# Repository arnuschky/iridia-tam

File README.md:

IRIDIA-TAM
==========

The IRIDIA TAM (Task Abstraction Module), a device whose function is to represent tasks that have to be performed by e-puck robots in laboratory experiments.

 * Website: http://arnuschky.github.com/iridia-tam/  
 * GitHub: https://github.com/arnuschky/iridia-tam/  
 * Repository: http://arnuschky.github.com/iridia-tam/  
 
Current version of the TAM: version 5, revision D.

The GitHub repository contains all files required for producing and using the TAM. In detail, the different directories contain:

3dmodel
-------

A 3D model of the TAM, created by using the free version of Google Sketchup (version 8). Models of the PCBs have been created using EagleUp (http://eagleup.wordpress.com/).

Additionally, the directory contains 2D plans of the plastic shell in PDF format. These plans were used to produce the plastic shell (machined from POM plastic).

coordinator
----------

This directory contains the coordinator, the central software written in Java that controls all TAMs in a given experiment. The researcher can use the coordinator software to set the behavior of the TAMs, define their interrelationships and collect statistics. Due to the use of Java, the software it platform-independent.

The directory also includes a modified version of the Xbee-api, an open-source project to access Xbee modules using Java. See http://code.google.com/p/xbee-api/ for more information. The project has been adapted to use the Digimesh mesh networking prototcol. If desired, one could also use simple point-to-point communication or the more advanced Zigbee prototcol.

electronics
-----------

This directory contains the project files created using Eagle (non-free version, due to PCB size) and the Arduino libraries and firmware.

### electronics/eagle

Contains the CAD files (board and schematics) for CADSoft Eagle (Version 6). 
Additionally, a library with custom footprints is also included in the repository.

### electronics/arduino

Sourcecode of the TAM's firmware ("sketchbook" in Arduino-speech). There are also a number of libraries included on which the firmware depends. Some of these libraries have been written or modified by us:

 - ircom - library that allows to communicate between the TAM and the epuck using the proximity sensor of the epuck
 - TLC59116 - generic TLC59116 library, adapted from http://brmlab.cz/project/ledbar (CC Attribution-Noncommercial-Share Alike 3.0 Unported License)
 - Xbee - library for using Xbee modules with the Arduino by Andrew Rapp, adapted to work with Digimesh networks and software serial ports (GPL 3)

Others are 3rd party open-source projects included for convenience:

 - I2C - fast I2C library by Wayne Truchsess (LGPL) http://dsscircuits.com/articles/arduino-i2c-master-library.html

photos
------

High-res photos of the TAM version 5, revision D.

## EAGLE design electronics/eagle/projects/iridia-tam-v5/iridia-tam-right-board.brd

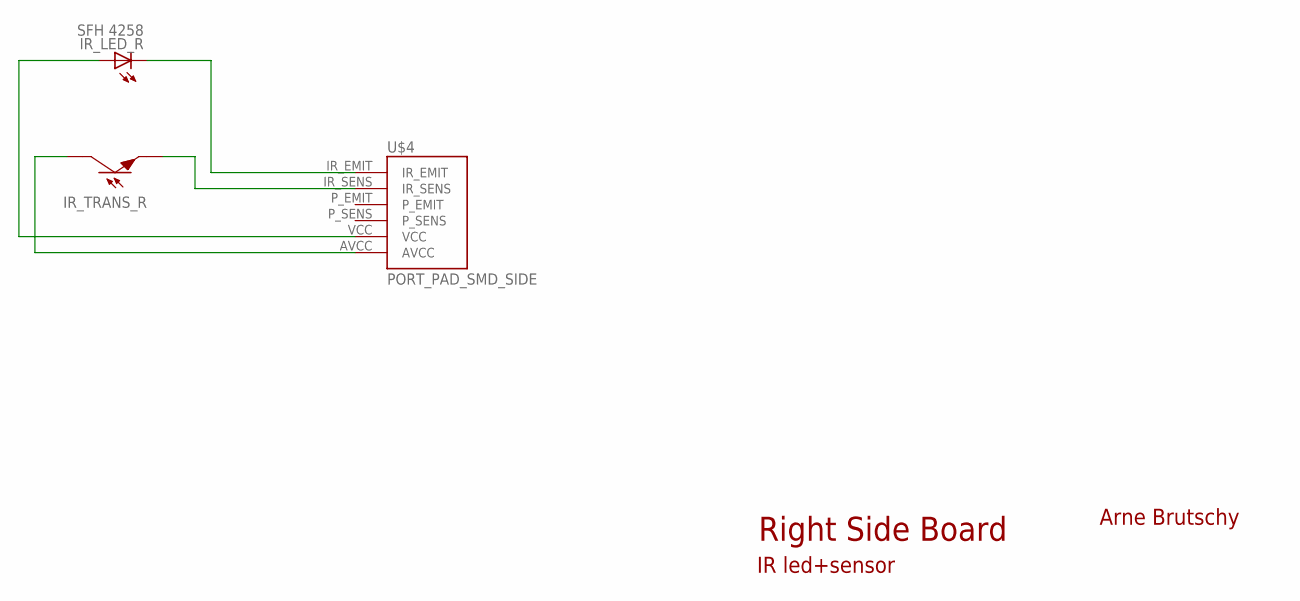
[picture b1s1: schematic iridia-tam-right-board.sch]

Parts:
IR_LED_R: SFH 4258; P-LCC-4-1C-3A
IR_TRANS_R: SFH 320 FA; P-LCC-2-TRANS
U$4: PORT_PAD_SMD_SIDE

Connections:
IR_EMIT_R: IR_LED_R.C@1 (C), U$4.IR_EMIT
IR_SENSE_R: IR_TRANS_R.E, U$4.IR_SENS
unnamed: IR_TRANS_R.COL, U$4.AVCC
VCC: IR_LED_R.A@2 (A), IR_LED_R.A@3 (A), IR_LED_R.A@4 (A), U$4.VCC

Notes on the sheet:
Right Side Board
IR led+sensor
Arne Brutschy

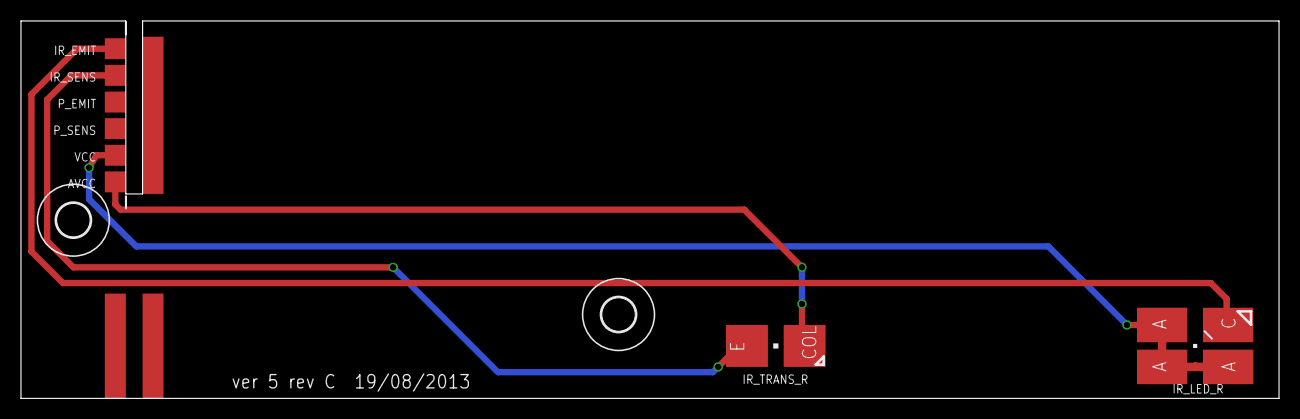
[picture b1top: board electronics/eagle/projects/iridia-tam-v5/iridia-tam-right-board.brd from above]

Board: 2 copper layers, 120.0 x 36.0 mm, 5 parts (0 on the bottom side), 4 nets.

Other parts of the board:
U$1, U$3: 3,2

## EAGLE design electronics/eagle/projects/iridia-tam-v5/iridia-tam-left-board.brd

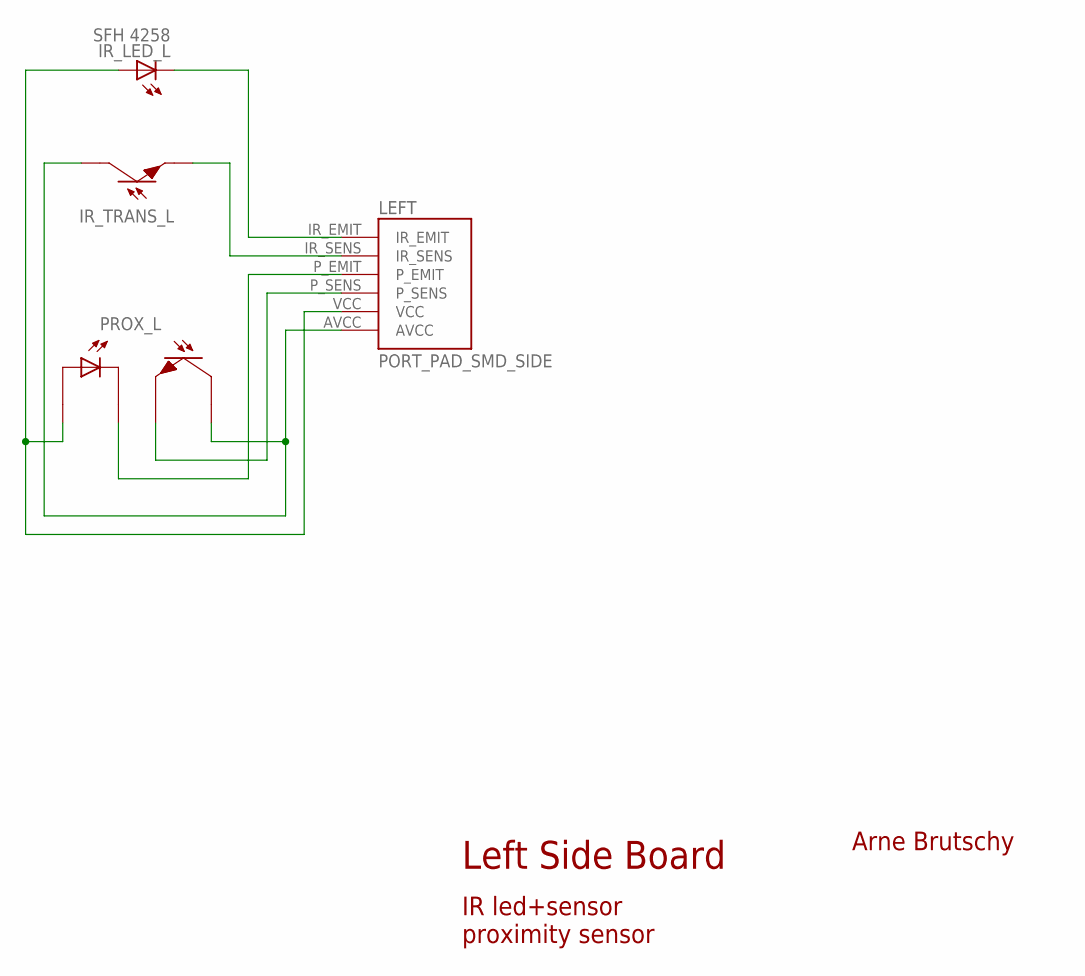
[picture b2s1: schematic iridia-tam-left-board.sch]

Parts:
IR_LED_L: SFH 4258; P-LCC-4-1C-3A
IR_TRANS_L: SFH 320 FA; P-LCC-2-TRANS
LEFT: PORT_PAD_SMD_SIDE
PROX_L: TCRT1000; TCRT1000_TH

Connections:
AVCC: IR_TRANS_L.COL, LEFT.AVCC, PROX_L.COL
IR_EMIT_L: IR_LED_L.C@1 (C), LEFT.IR_EMIT
IR_SENSE_L: IR_TRANS_L.E, LEFT.IR_SENS
PROX_EMIT: LEFT.P_EMIT, PROX_L.CAT
PROX_SENSE: LEFT.P_SENS, PROX_L.E
VCC: IR_LED_L.A@2 (A), IR_LED_L.A@3 (A), IR_LED_L.A@4 (A), LEFT.VCC, PROX_L.A

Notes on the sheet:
Left Side Board
IR led+sensor proximity sensor
Arne Brutschy

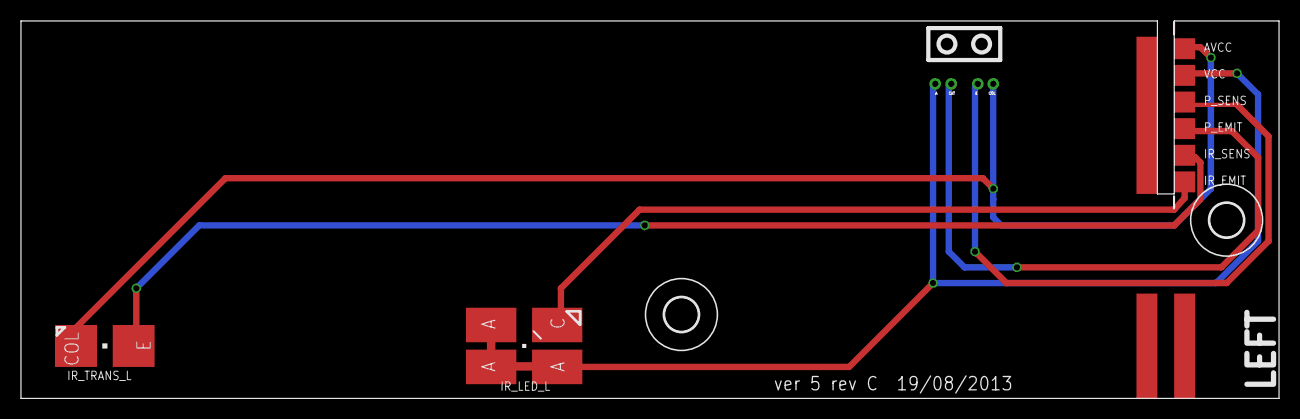
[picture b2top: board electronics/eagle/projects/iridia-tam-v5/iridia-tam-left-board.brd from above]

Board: 2 copper layers, 120.0 x 36.0 mm, 6 parts (0 on the bottom side), 6 nets.

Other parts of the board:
U$2, U$3: 3,2

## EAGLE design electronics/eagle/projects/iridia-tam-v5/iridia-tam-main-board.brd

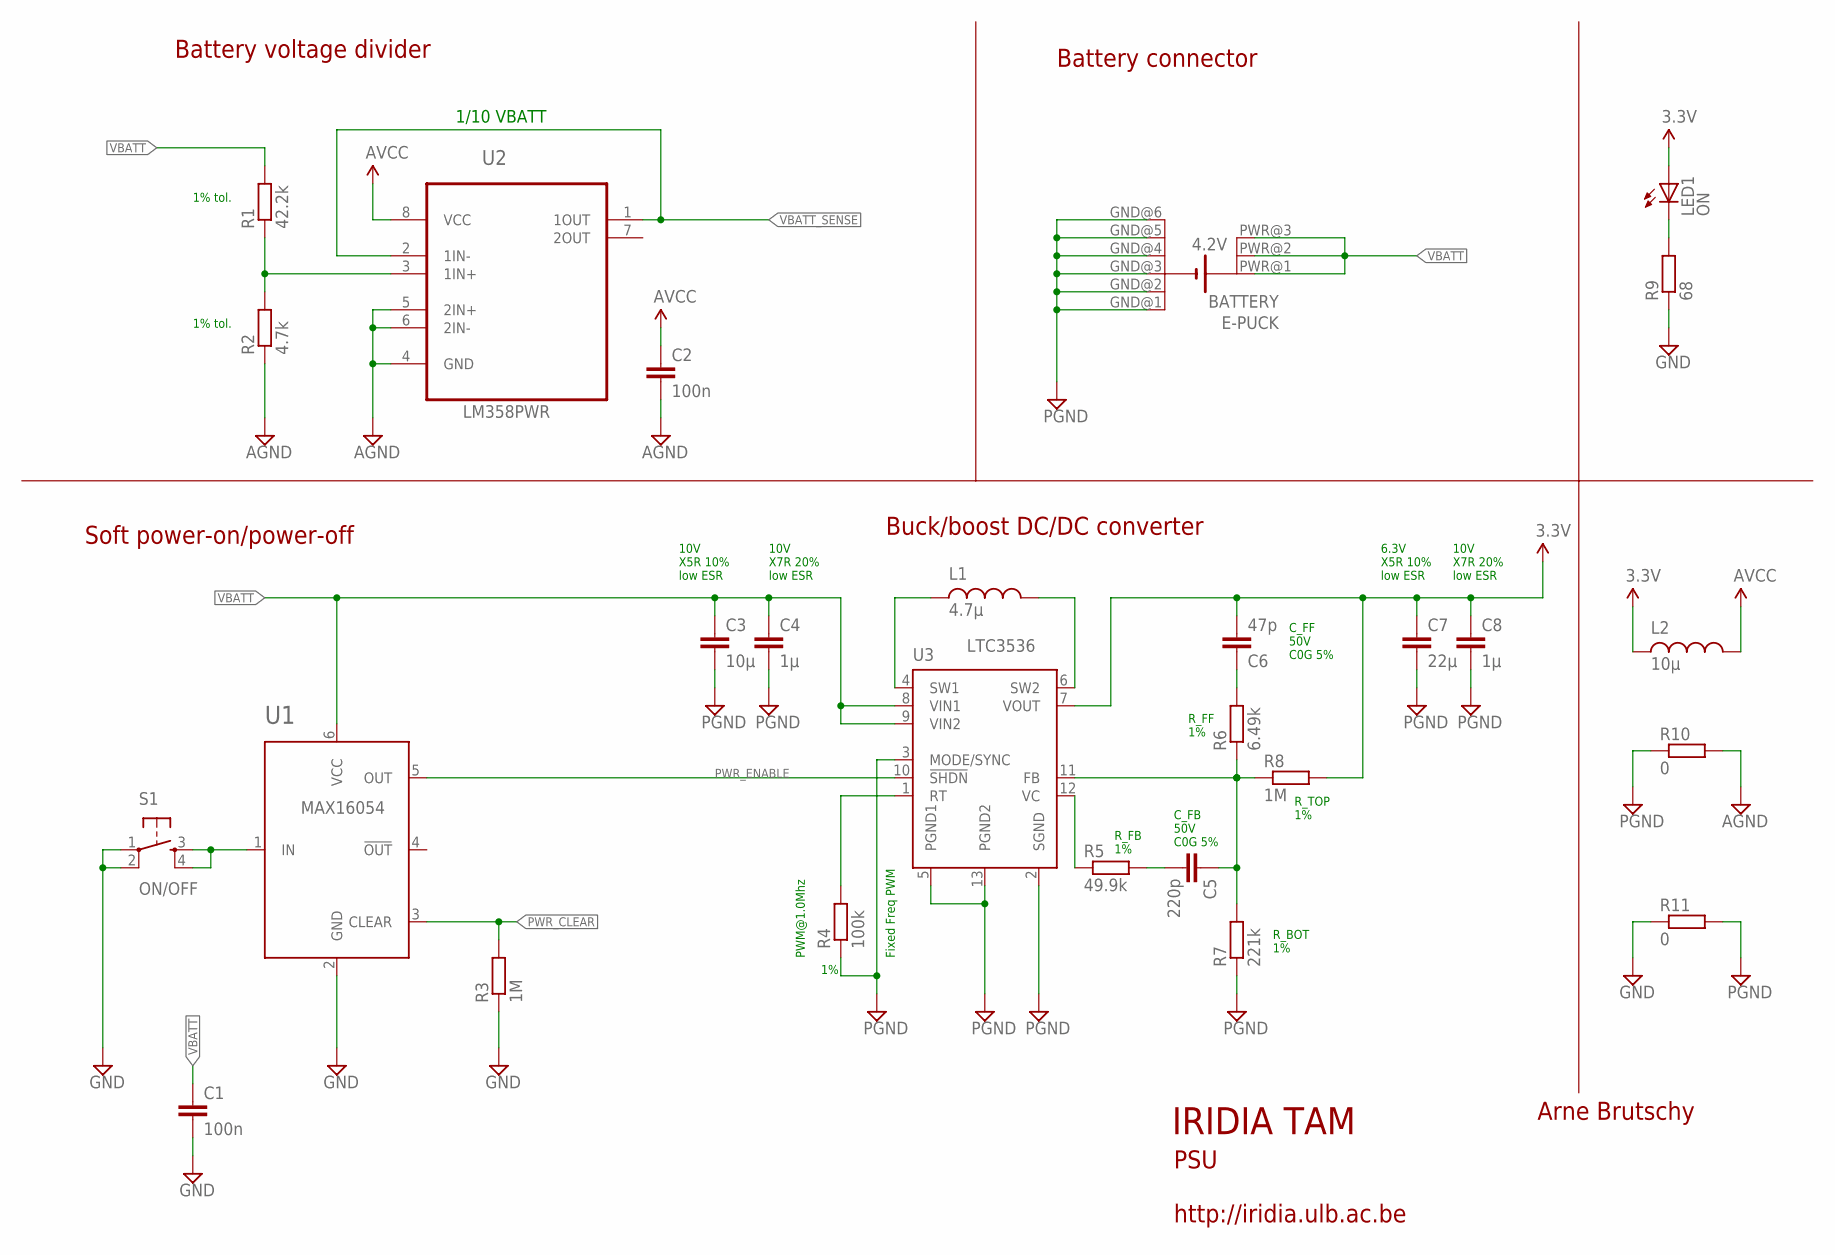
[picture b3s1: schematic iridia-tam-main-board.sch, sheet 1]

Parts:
C1, C2: 100n; C0603
C3: 10µ; C0805
C4, C8: 1µ; C0603
C5: 220p; C0603
C6: 47p; C0603
C7: 22µ; C1206
JP1: EPUCK_BATTERY
L1: 4.7µ; TDK-VLCF
L2: 10µ; L0805
LED1: ON; CHIPLED_1206
R1: 42.2k; R0603
R2: 4.7k; R0603
R3, R8: 1M; R0603
R4: 100k; R0603
R5: 49.9k; R0603
R6: 6.49k; R0603
R7: 221k; R0603
R9: 68; R0603
R10, R11: 0; R0603
S1: ON/OFF; TACTILE_SWITCH_SMD
U1: MAX16054; SOT23-6-INV
U2: LM358PW; SOP65P640X120-8N
U3: LTC3536; MSOP12-EP

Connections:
AGND: C2.2, R2.1, R10.2, U2.4 (GND), U2.5 (2IN+), U2.6 (2IN-); also elsewhere on the board
AVCC: C2.1, L2.2, U2.8 (VCC); also elsewhere on the board
GND: C1.2, R3.1, R9.1, R11.1, S1.1, S1.2, U1.2 (GND); also elsewhere on the board
unnamed: C6.1, R6.2
unnamed: R4.2, U3.1 (RT)
unnamed: R1.1, R2.2, U2.3 (1IN+)
unnamed: LED1.C, R9.2
unnamed: L1.P$1, U3.4 (SW1)
unnamed: L1.P$2, U3.6 (SW2)
unnamed: S1.3, S1.4, U1.1 (IN)
unnamed: R5.1, U3.12 (VC)
unnamed: C5.1, R6.1, R7.2, R8.1, U3.11 (FB)
unnamed: C5.2, R5.2
PGND: C3.2, C4.2, C7.2, C8.2, JP1.GND@1 (-1), JP1.GND@2 (-2), JP1.GND@3 (-3), JP1.GND@4 (-4), JP1.GND@5 (-5), JP1.GND@6 (-6), R4.1, R7.1, R10.1, R11.2, U3.2 (SGND), U3.3 (MODE/SYNC), U3.5 (PGND1), U3.13 (PGND2); also elsewhere on the board
PWR_CLEAR: R3.2, U1.3 (CLEAR); also elsewhere on the board
PWR_ENABLE: U1.5 (OUT), U3.10 (!SHDN)
VBATT: C1.1, C3.1, C4.1, JP1.PWR@1 (+1), JP1.PWR@2 (+2), JP1.PWR@3 (+3), R1.2, U1.6 (VCC), U3.8 (VIN1), U3.9 (VIN2); also elsewhere on the board
VBATT_SENSE: U2.1 (1OUT), U2.2 (1IN-); also elsewhere on the board
VCC: C6.2, C7.1, C8.1, L2.1, LED1.A, R8.2, U3.7 (VOUT); also elsewhere on the board

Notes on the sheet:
IRIDIA TAM
Arne Brutschy
http://iridia.ulb.ac.be
PSU
PWM@1.0Mhz
R_FF 1%
C_FF 50V C0G 5%
R_TOP 1%
R_FB 1%
C_FB 50V C0G 5%
R_BOT 1%
1/10 VBATT
Battery voltage divider
LM358PWR
Battery connector
Buck/boost DC/DC converter
Soft power-on/power-off
LTC3536
1% tol.
6.3V X5R 10% low ESR
Fixed Freq PWM
10V X7R 20% low ESR
10V X5R 10% low ESR

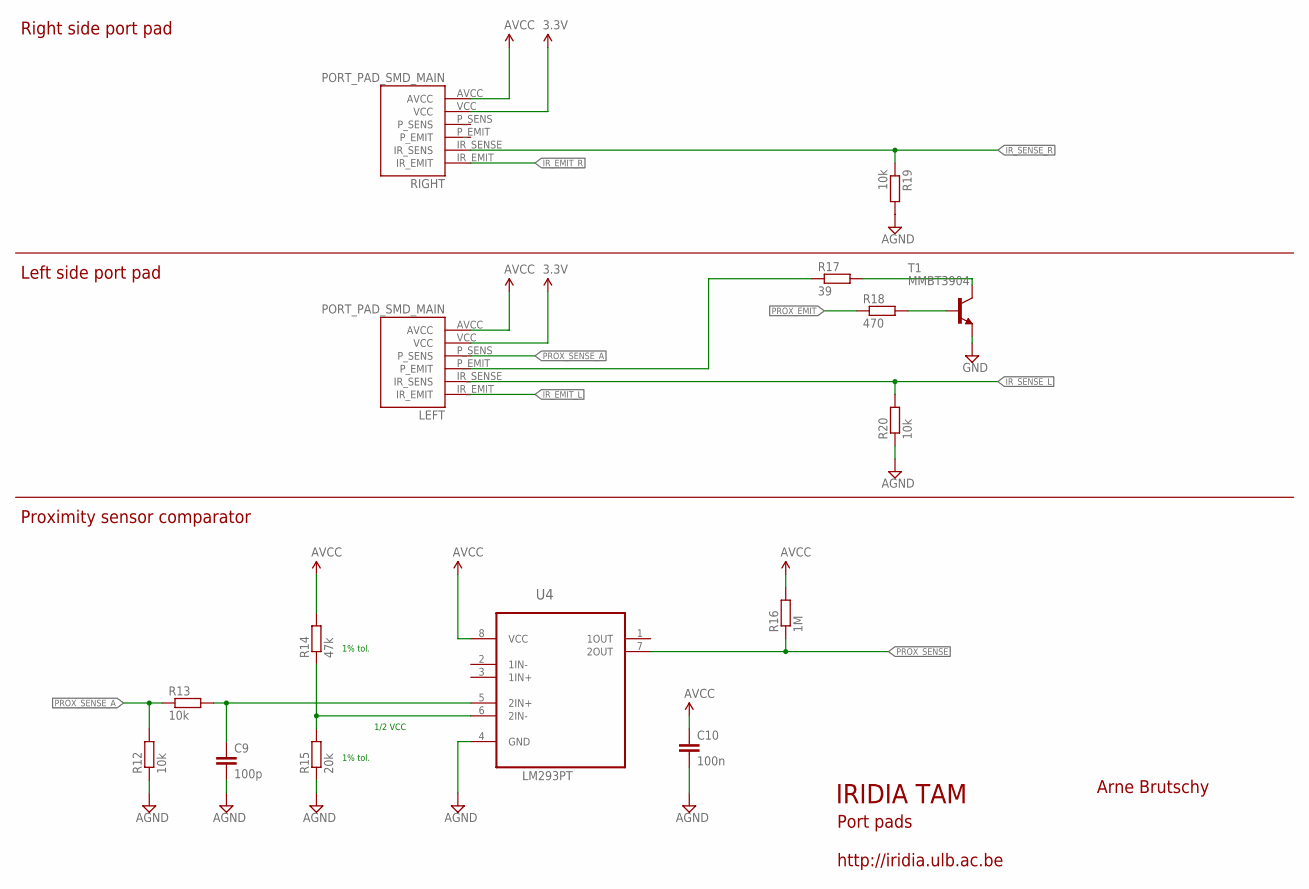
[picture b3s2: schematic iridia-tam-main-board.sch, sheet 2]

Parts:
C9: 100p; C0603
C10: 100n; C0603
LEFT: PORT_PAD_SMD_MAIN
R12, R13, R19, R20: 10k; R0603
R14: 47k; R0603
R15: 20k; R0603
R16: 1M; R0603
R17: 39; R0603
R18: 470; R0603
RIGHT: PORT_PAD_SMD_MAIN
T1: MMBT3904; SOT23-BEC
U4: LM293PT; 8-TSSOP_4.4MM

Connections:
AGND: C9.2, C10.2, R12.1, R15.1, R19.2, R20.1, U4.4 (GND); also elsewhere on the board
AVCC: C10.1, LEFT.AVCC, R14.2, R16.2, RIGHT.AVCC, U4.8 (VCC); also elsewhere on the board
GND: T1.E; also elsewhere on the board
IR_EMIT_L: LEFT.IR_EMIT; also elsewhere on the board
IR_EMIT_R: RIGHT.IR_EMIT; also elsewhere on the board
IR_SENSE_L: LEFT.IR_SENSE (IR_SENS), R20.2; also elsewhere on the board
IR_SENSE_R: R19.1, RIGHT.IR_SENSE (IR_SENS); also elsewhere on the board
unnamed: LEFT.P_EMIT, R17.1
unnamed: R14.1, R15.2, U4.6 (2IN-)
unnamed: R18.2, T1.B
unnamed: R17.2, T1.C
PROX_EMIT: R18.1; also elsewhere on the board
PROX_SENSE: R16.1, U4.7 (2OUT); also elsewhere on the board
PROX_SENSE_A: LEFT.P_SENS, R12.2, R13.1; also elsewhere on the board
PROX_SENSE_S: C9.1, R13.2, U4.5 (2IN+); also elsewhere on the board
VCC: LEFT.VCC, RIGHT.VCC; also elsewhere on the board

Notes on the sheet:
IRIDIA TAM
Arne Brutschy
http://iridia.ulb.ac.be
Port pads
1/2 VCC
Proximity sensor comparator
LM293PT
Left side port pad
Right side port pad
1% tol.

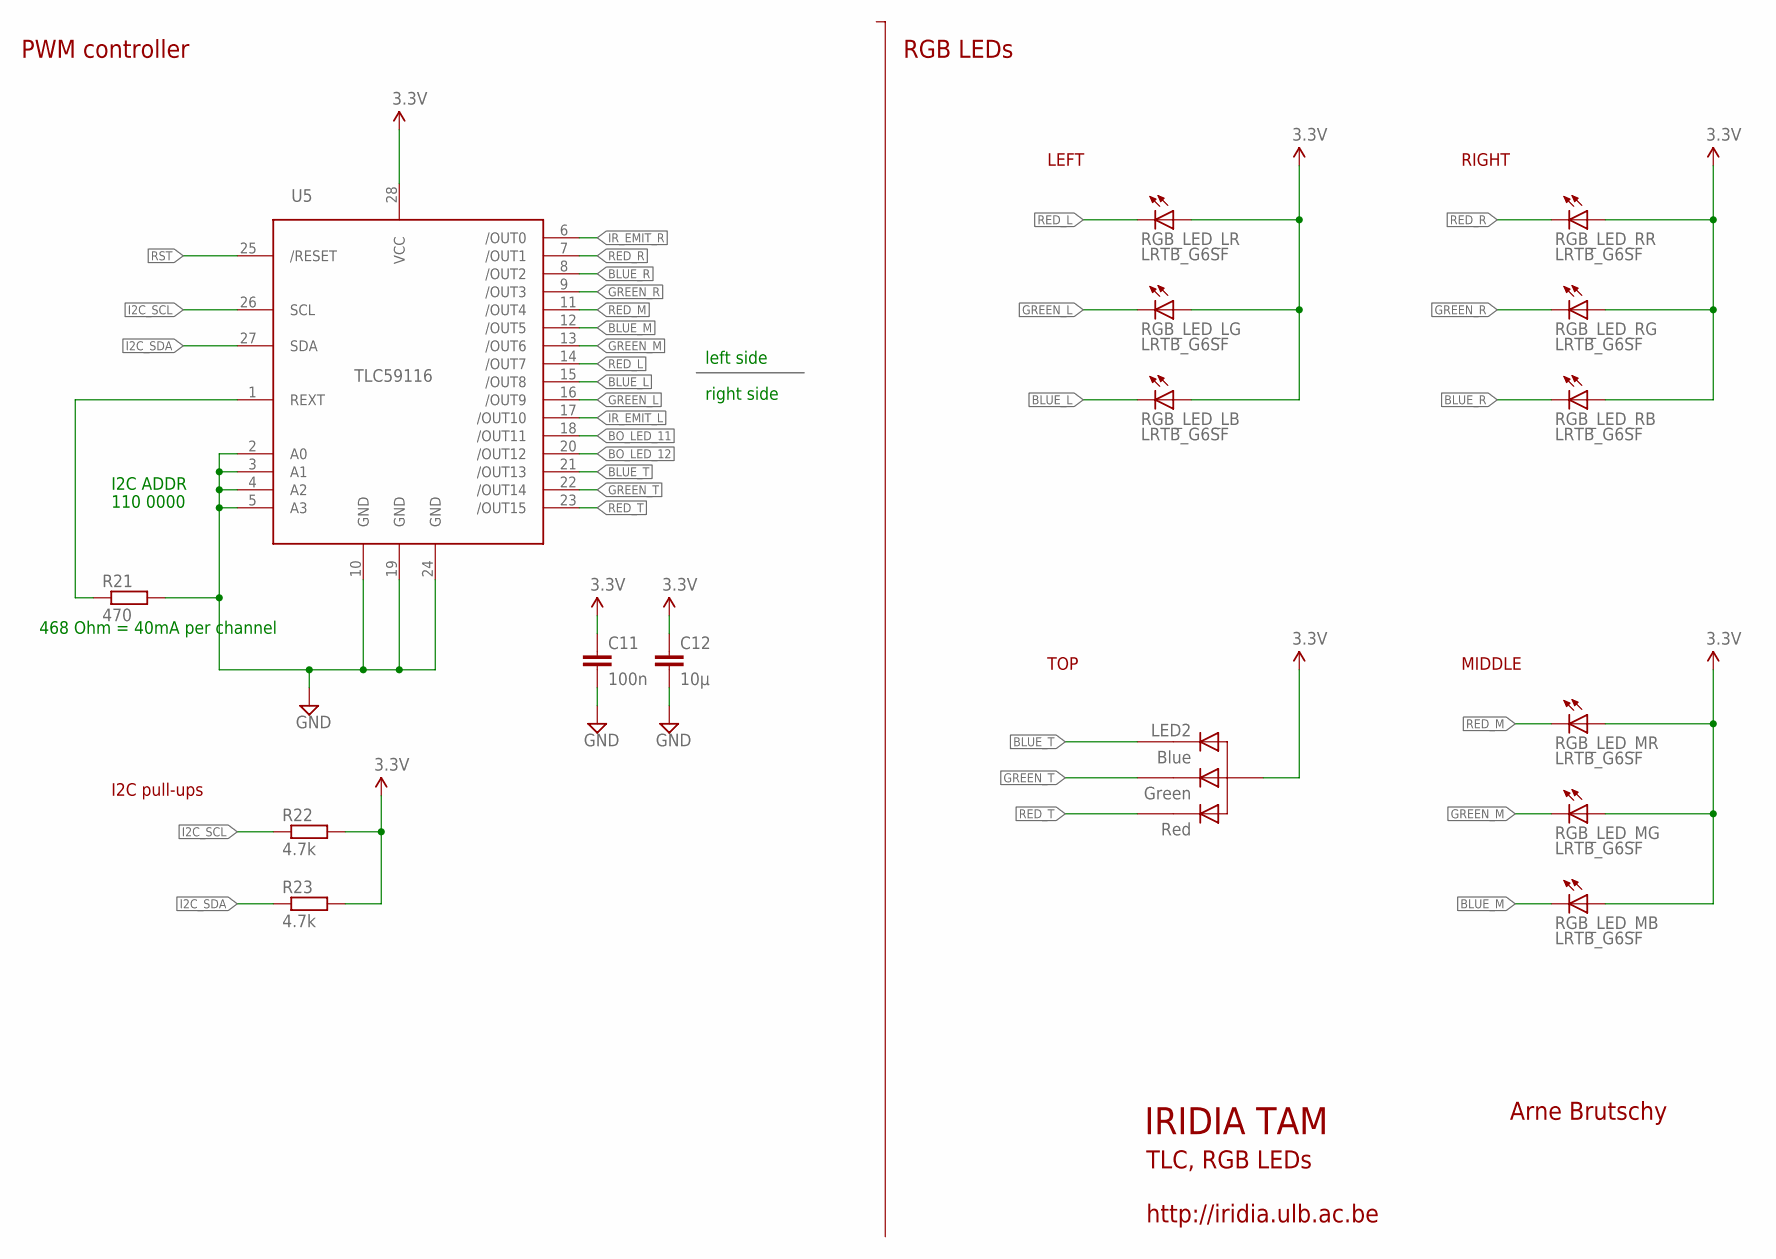
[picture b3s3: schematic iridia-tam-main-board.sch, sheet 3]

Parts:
C11: 100n; C0603
C12: 10µ; C0805
LED2: RGBLED_CA5MMTROUGHHOLE; LED5MMRGB
R21: 470; R0603
R22, R23: 4.7k; R0603
RGB_LED_L: LRTB_G6SF; P-LCC-6_TOPLED
RGB_LED_M: LRTB_G6SF; P-LCC-6_TOPLED
RGB_LED_R: LRTB_G6SF; P-LCC-6_TOPLED
U5: TLC59116-TSSOP; TSSOP28

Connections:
BLUE_L: RGB_LED_L.C3 (C), U5.15 (/OUT8)
BLUE_M: RGB_LED_M.C3 (C), U5.12 (/OUT5)
BLUE_R: RGB_LED_R.C3 (C), U5.8 (/OUT2)
BLUE_T: LED2.4 (CB), U5.21 (/OUT13)
BO_LED_11: U5.18 (/OUT11); also elsewhere on the board
BO_LED_12: U5.20 (/OUT12); also elsewhere on the board
GND: C11.2, C12.2, R21.2, U5.2 (A0), U5.3 (A1), U5.4 (A2), U5.5 (A3), U5.10 (GND), U5.19 (GND), U5.24 (GND); also elsewhere on the board
GREEN_L: RGB_LED_L.C2 (C), U5.16 (/OUT9)
GREEN_M: RGB_LED_M.C2 (C), U5.13 (/OUT6)
GREEN_R: RGB_LED_R.C2 (C), U5.9 (/OUT3)
GREEN_T: LED2.3 (CG), U5.22 (/OUT14)
I2C_SCL: R22.1, U5.26 (SCL); also elsewhere on the board
I2C_SDA: R23.1, U5.27 (SDA); also elsewhere on the board
IR_EMIT_L: U5.17 (/OUT10); also elsewhere on the board
IR_EMIT_R: U5.6 (/OUT0); also elsewhere on the board
RED_L: RGB_LED_L.C1 (C), U5.14 (/OUT7)
RED_M: RGB_LED_M.C1 (C), U5.11 (/OUT4)
RED_R: RGB_LED_R.C1 (C), U5.7 (/OUT1)
RED_T: LED2.1 (CR), U5.23 (/OUT15)
REXT: R21.1, U5.1 (REXT)
RST: U5.25 (/RESET); also elsewhere on the board
VCC: C11.1, C12.1, LED2.2 (A), R22.2, R23.2, RGB_LED_L.A1 (A), RGB_LED_L.A2 (A), RGB_LED_L.A3 (A), RGB_LED_M.A1 (A), RGB_LED_M.A2 (A), RGB_LED_M.A3 (A), RGB_LED_R.A1 (A), RGB_LED_R.A2 (A), RGB_LED_R.A3 (A), U5.28 (VCC); also elsewhere on the board

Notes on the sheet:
IRIDIA TAM
Arne Brutschy
http://iridia.ulb.ac.be
TLC, RGB LEDs
LEFT
RIGHT
MIDDLE
TOP
I2C ADDR
110 0000
468 Ohm = 40mA per channel
I2C pull-ups
PWM controller
RGB LEDs
left side
right side

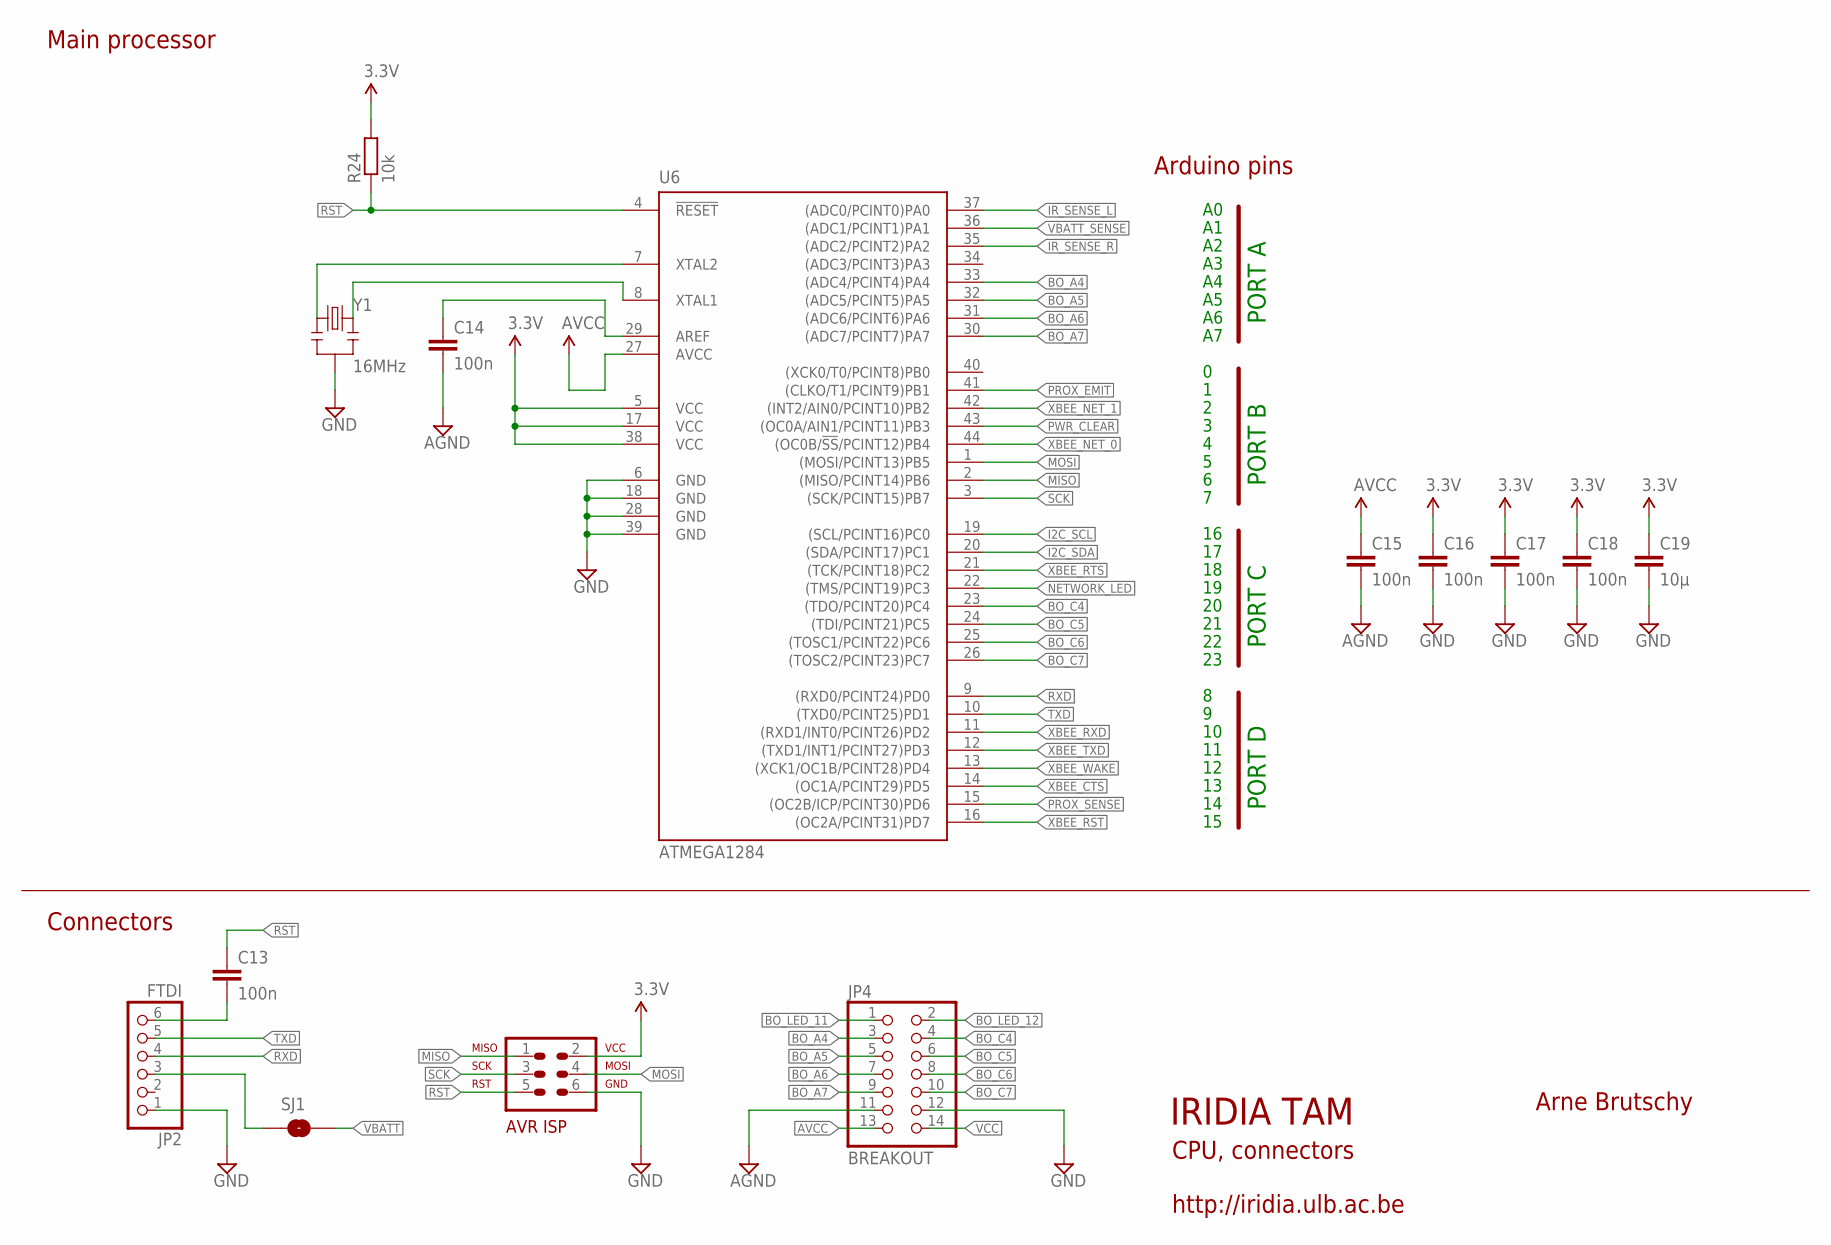
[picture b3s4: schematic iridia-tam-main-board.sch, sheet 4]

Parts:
C13, C14, C15, C16, C17, C18: 100n; C0603
C19: 10µ; C0805
JP2: FTDI; 1X06SMD/90
JP3: ISP; AVR-ISP-6
JP4: BREAKOUT; 2X07SMD
R24: 10k; R0603
SJ1: SOLDERJUMPERTRACE; SJ_2S-TRACE
U6: ATMEGA1284; TQFP44
Y1: 16MHz; RESONATOR-SMD

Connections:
AGND: C14.2, C15.2, JP4.11; also elsewhere on the board
AREF: C14.1, U6.29 (AREF)
AVCC: C15.1, JP4.13, U6.27 (AVCC); also elsewhere on the board
BO_A4: JP4.3, U6.33 ((ADC4/PCINT4)PA4)
BO_A5: JP4.5, U6.32 ((ADC5/PCINT5)PA5)
BO_A6: JP4.7, U6.31 ((ADC6/PCINT6)PA6)
BO_A7: JP4.9, U6.30 ((ADC7/PCINT7)PA7)
BO_C4: JP4.4, U6.23 ((TDO/PCINT20)PC4)
BO_C5: JP4.6, U6.24 ((TDI/PCINT21)PC5)
BO_C6: JP4.8, U6.25 ((TOSC1/PCINT22)PC6)
BO_C7: JP4.10, U6.26 ((TOSC2/PCINT23)PC7)
BO_LED_11: JP4.1; also elsewhere on the board
BO_LED_12: JP4.2; also elsewhere on the board
FTDI_RST1: C13.2, JP2.6
GND: C16.2, C17.2, C18.2, C19.2, JP2.1, JP3.6, JP4.12, U6.6 (GND), U6.18 (GND), U6.28 (GND), U6.39 (GND), Y1.2; also elsewhere on the board
I2C_SCL: U6.19 ((SCL/PCINT16)PC0); also elsewhere on the board
I2C_SDA: U6.20 ((SDA/PCINT17)PC1); also elsewhere on the board
IR_SENSE_L: U6.37 ((ADC0/PCINT0)PA0); also elsewhere on the board
IR_SENSE_R: U6.35 ((ADC2/PCINT2)PA2); also elsewhere on the board
MISO: JP3.1, U6.2 ((MISO/PCINT14)PB6)
MOSI: JP3.4, U6.1 ((MOSI/PCINT13)PB5)
unnamed: JP2.3, SJ1.1
NETWORK_LED: U6.22 ((TMS/PCINT19)PC3); also elsewhere on the board
PROX_EMIT: U6.41 ((CLKO/T1/PCINT9)PB1); also elsewhere on the board
PROX_SENSE: U6.15 ((OC2B/ICP/PCINT30)PD6); also elsewhere on the board
PWR_CLEAR: U6.43 ((OC0A/AIN1/PCINT11)PB3); also elsewhere on the board
RST: C13.1, JP3.5, R24.1, U6.4 (!RESET); also elsewhere on the board
RXD: JP2.4, U6.9 ((RXD0/PCINT24)PD0)
SCK: JP3.3, U6.3 ((SCK/PCINT15)PB7)
TXD: JP2.5, U6.10 ((TXD0/PCINT25)PD1)
VBATT: SJ1.2; also elsewhere on the board
VBATT_SENSE: U6.36 ((ADC1/PCINT1)PA1); also elsewhere on the board
VCC: C16.1, C17.1, C18.1, C19.1, JP3.2, JP4.14, R24.2, U6.5 (VCC), U6.17 (VCC), U6.38 (VCC); also elsewhere on the board
XBEE_CTS: U6.14 ((OC1A/PCINT29)PD5); also elsewhere on the board
XBEE_NET_0: U6.44 ((OC0B/!SS!/PCINT12)PB4); also elsewhere on the board
XBEE_NET_1: U6.42 ((INT2/AIN0/PCINT10)PB2); also elsewhere on the board
XBEE_RST: U6.16 ((OC2A/PCINT31)PD7); also elsewhere on the board
XBEE_RTS: U6.21 ((TCK/PCINT18)PC2); also elsewhere on the board
XBEE_RXD: U6.11 ((RXD1/INT0/PCINT26)PD2); also elsewhere on the board
XBEE_TXD: U6.12 ((TXD1/INT1/PCINT27)PD3); also elsewhere on the board
XBEE_WAKE: U6.13 ((XCK1/OC1B/PCINT28)PD4); also elsewhere on the board
Y1_1: U6.7 (XTAL2), Y1.1
Y1_2: U6.8 (XTAL1), Y1.3

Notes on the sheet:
IRIDIA TAM
Arne Brutschy
http://iridia.ulb.ac.be
CPU, connectors
Main processor
Connectors
Arduino pins
PORT A
PORT B
PORT C
PORT D

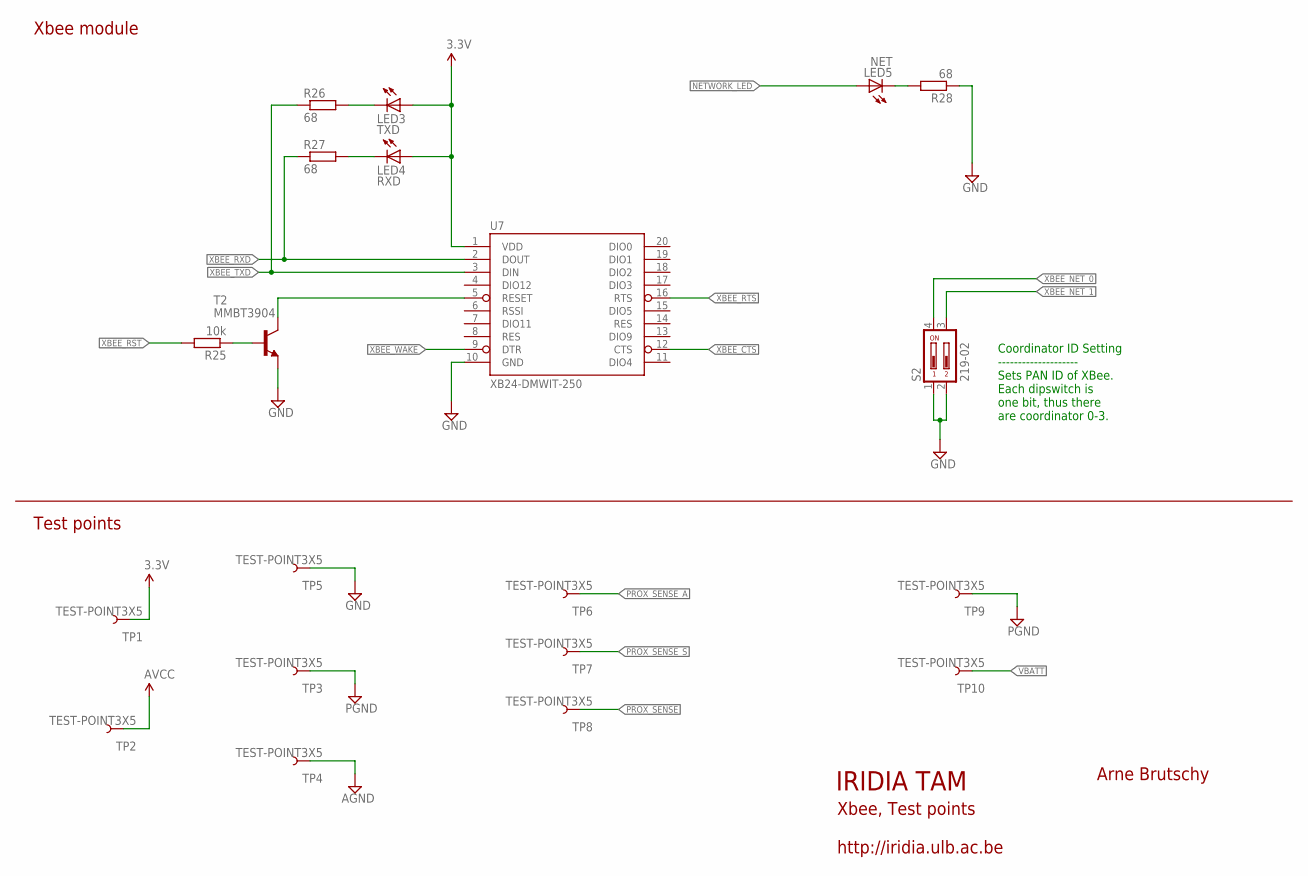
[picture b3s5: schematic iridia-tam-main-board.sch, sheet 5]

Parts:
LED3: TXD; CHIPLED_0805
LED4: RXD; CHIPLED_0805
LED5: NET; CHIPLED_0805
R25: 10k; R0603
R26, R27, R28: 68; R0603
S2: 219-02; CTS-219-02
T2: MMBT3904; SOT23-BEC
TP1, TP2, TP3, TP4, TP5, TP6, TP7, TP8, TP9, TP10: TEST-POINT3X5; PAD.03X.05
U7: XB24-DMWIT-250; XBEE-SMD

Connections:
AGND: TP4.P$1; also elsewhere on the board
AVCC: TP2.P$1; also elsewhere on the board
GND: R28.1, S2.1, S2.2, T2.E, TP5.P$1, U7.10 (GND); also elsewhere on the board
unnamed: LED4.C, R27.2
unnamed: R25.1, T2.B
unnamed: LED3.C, R26.2
unnamed: T2.C, U7.5 (RESET)
unnamed: LED5.C, R28.2
NETWORK_LED: LED5.A; also elsewhere on the board
PGND: TP3.P$1, TP9.P$1; also elsewhere on the board
PROX_SENSE: TP8.P$1; also elsewhere on the board
PROX_SENSE_A: TP6.P$1; also elsewhere on the board
PROX_SENSE_S: TP7.P$1; also elsewhere on the board
VBATT: TP10.P$1; also elsewhere on the board
VCC: LED3.A, LED4.A, TP1.P$1, U7.1 (VDD); also elsewhere on the board
XBEE_CTS: U7.12 (CTS); also elsewhere on the board
XBEE_NET_0: S2.4; also elsewhere on the board
XBEE_NET_1: S2.3; also elsewhere on the board
XBEE_RST: R25.2; also elsewhere on the board
XBEE_RTS: U7.16 (RTS); also elsewhere on the board
XBEE_RXD: R27.1, U7.2 (DOUT); also elsewhere on the board
XBEE_TXD: R26.1, U7.3 (DIN); also elsewhere on the board
XBEE_WAKE: U7.9 (DTR); also elsewhere on the board

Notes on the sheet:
Xbee module
IRIDIA TAM
Arne Brutschy
http://iridia.ulb.ac.be
Xbee, Test points
Test points
Coordinator ID Setting -------------------- Sets PAN ID of XBee. Each dipswitch is one bit, thus there are coordinator 0-3.

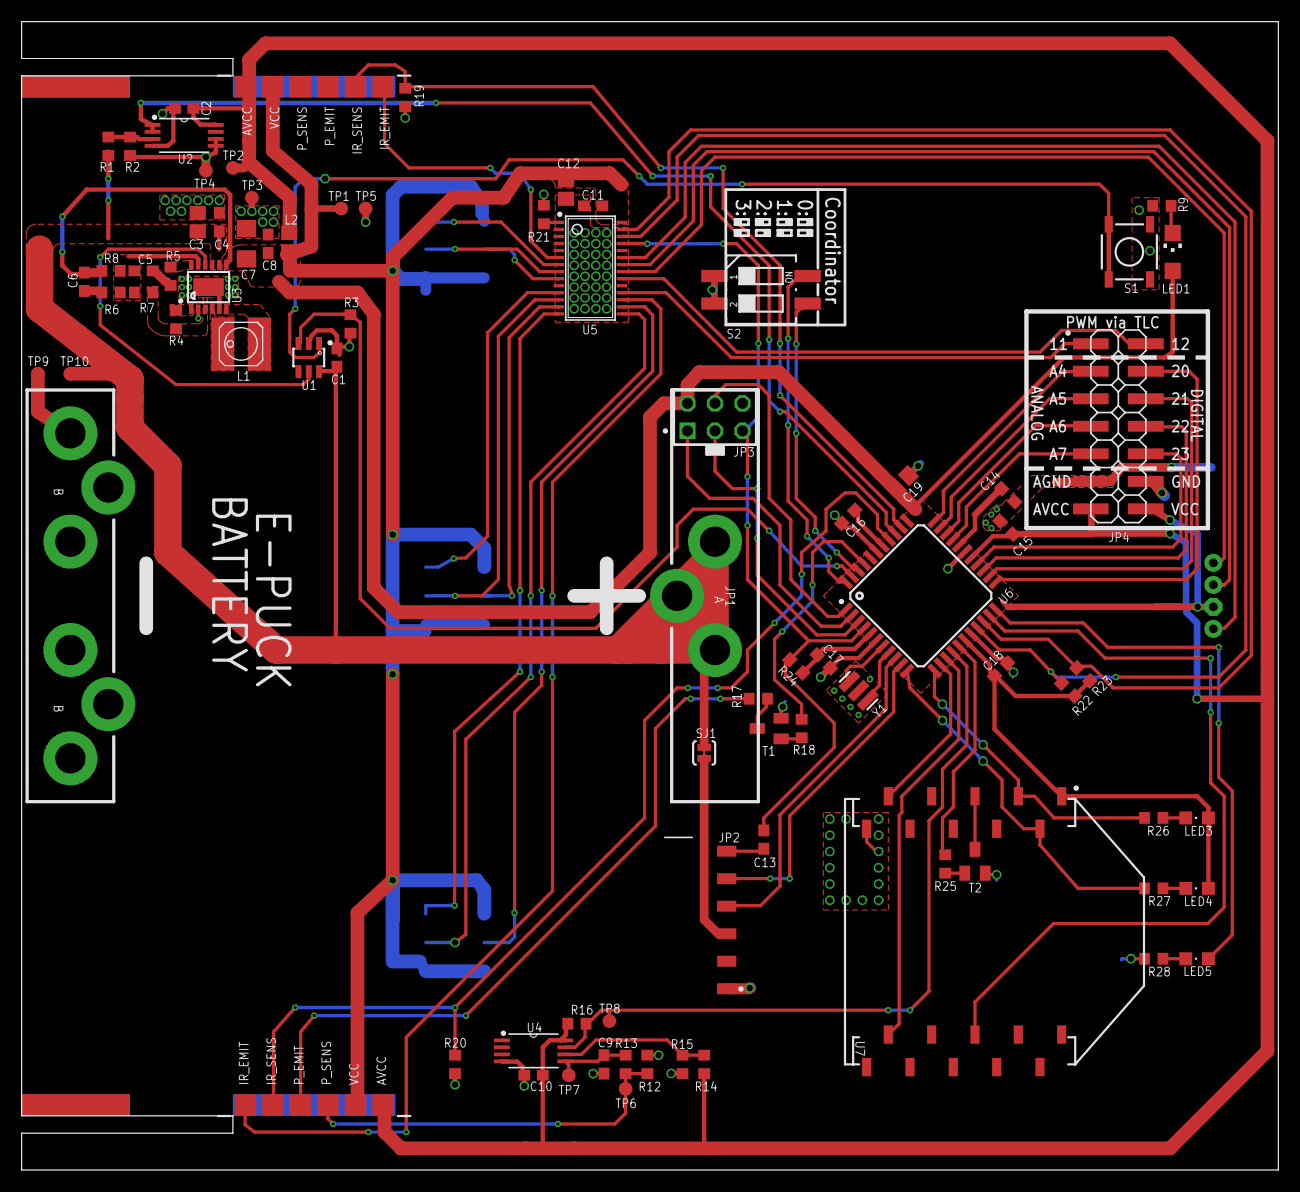
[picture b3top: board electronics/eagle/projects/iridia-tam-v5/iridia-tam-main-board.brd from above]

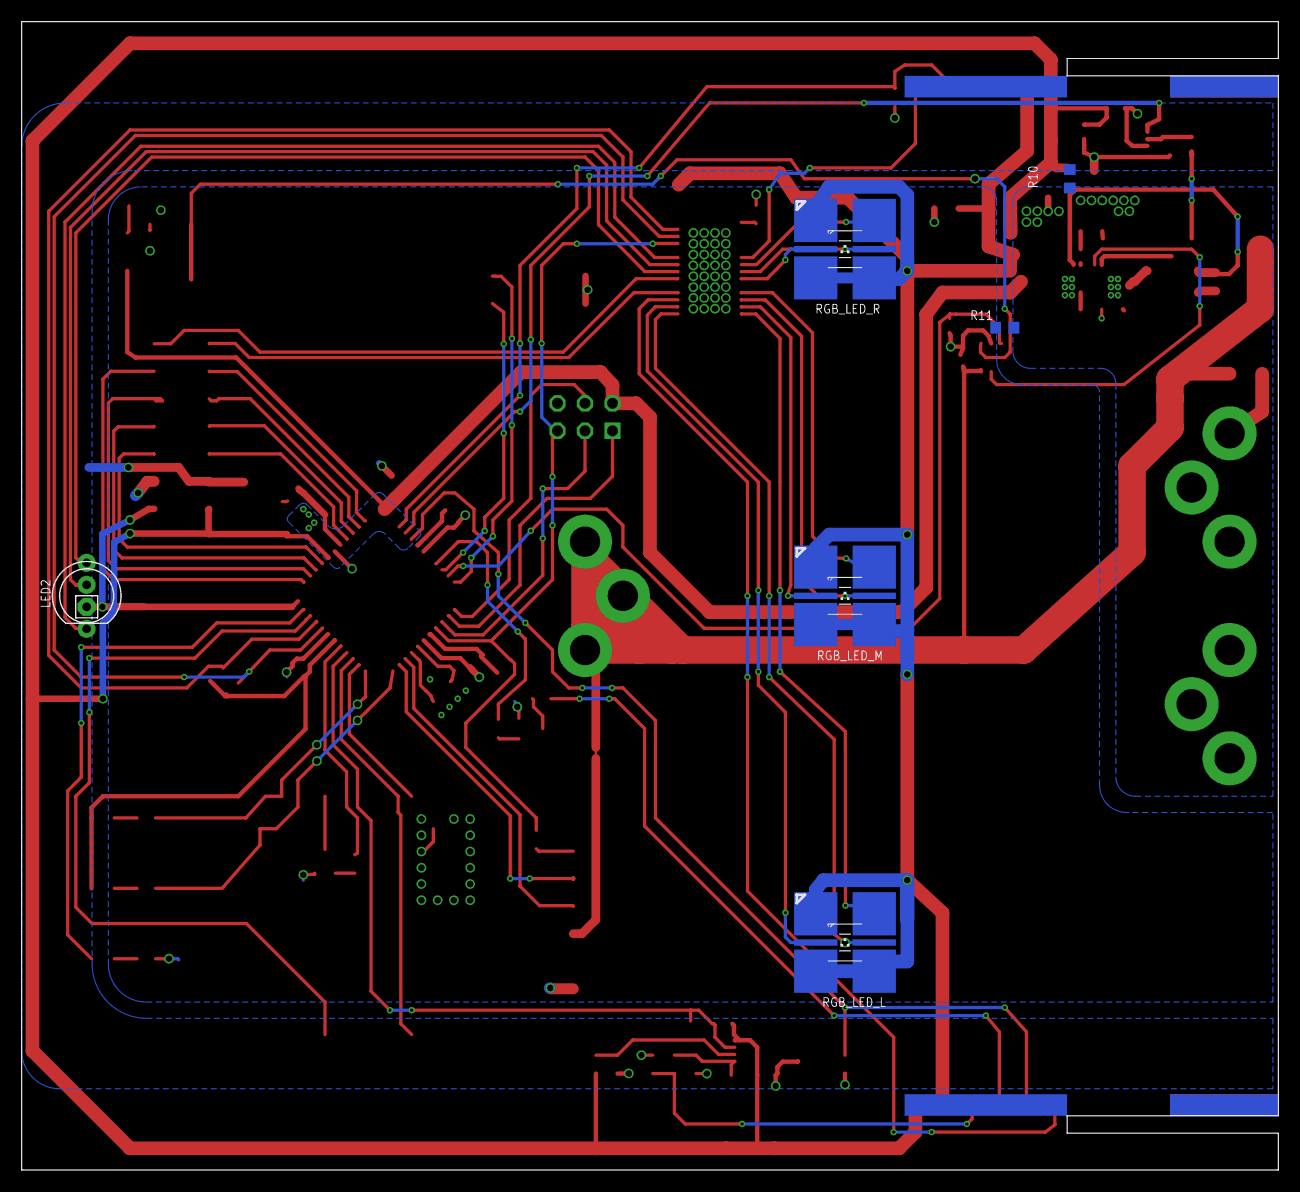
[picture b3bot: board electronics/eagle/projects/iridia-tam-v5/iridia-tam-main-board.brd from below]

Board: 2 copper layers, 116.0 x 106.0 mm, 86 parts (6 on the bottom side), 81 nets.

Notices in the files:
electronics/eagle/projects/iridia-tam-v4/iridia-tam-main-board.brd:
CC BY-SA 3.0
Creative Commons
parts and their libraries:
SparkFun-RF: Licensing: CC v3.0 Share-Alike You are welcome to use this library for commercial purposes.
